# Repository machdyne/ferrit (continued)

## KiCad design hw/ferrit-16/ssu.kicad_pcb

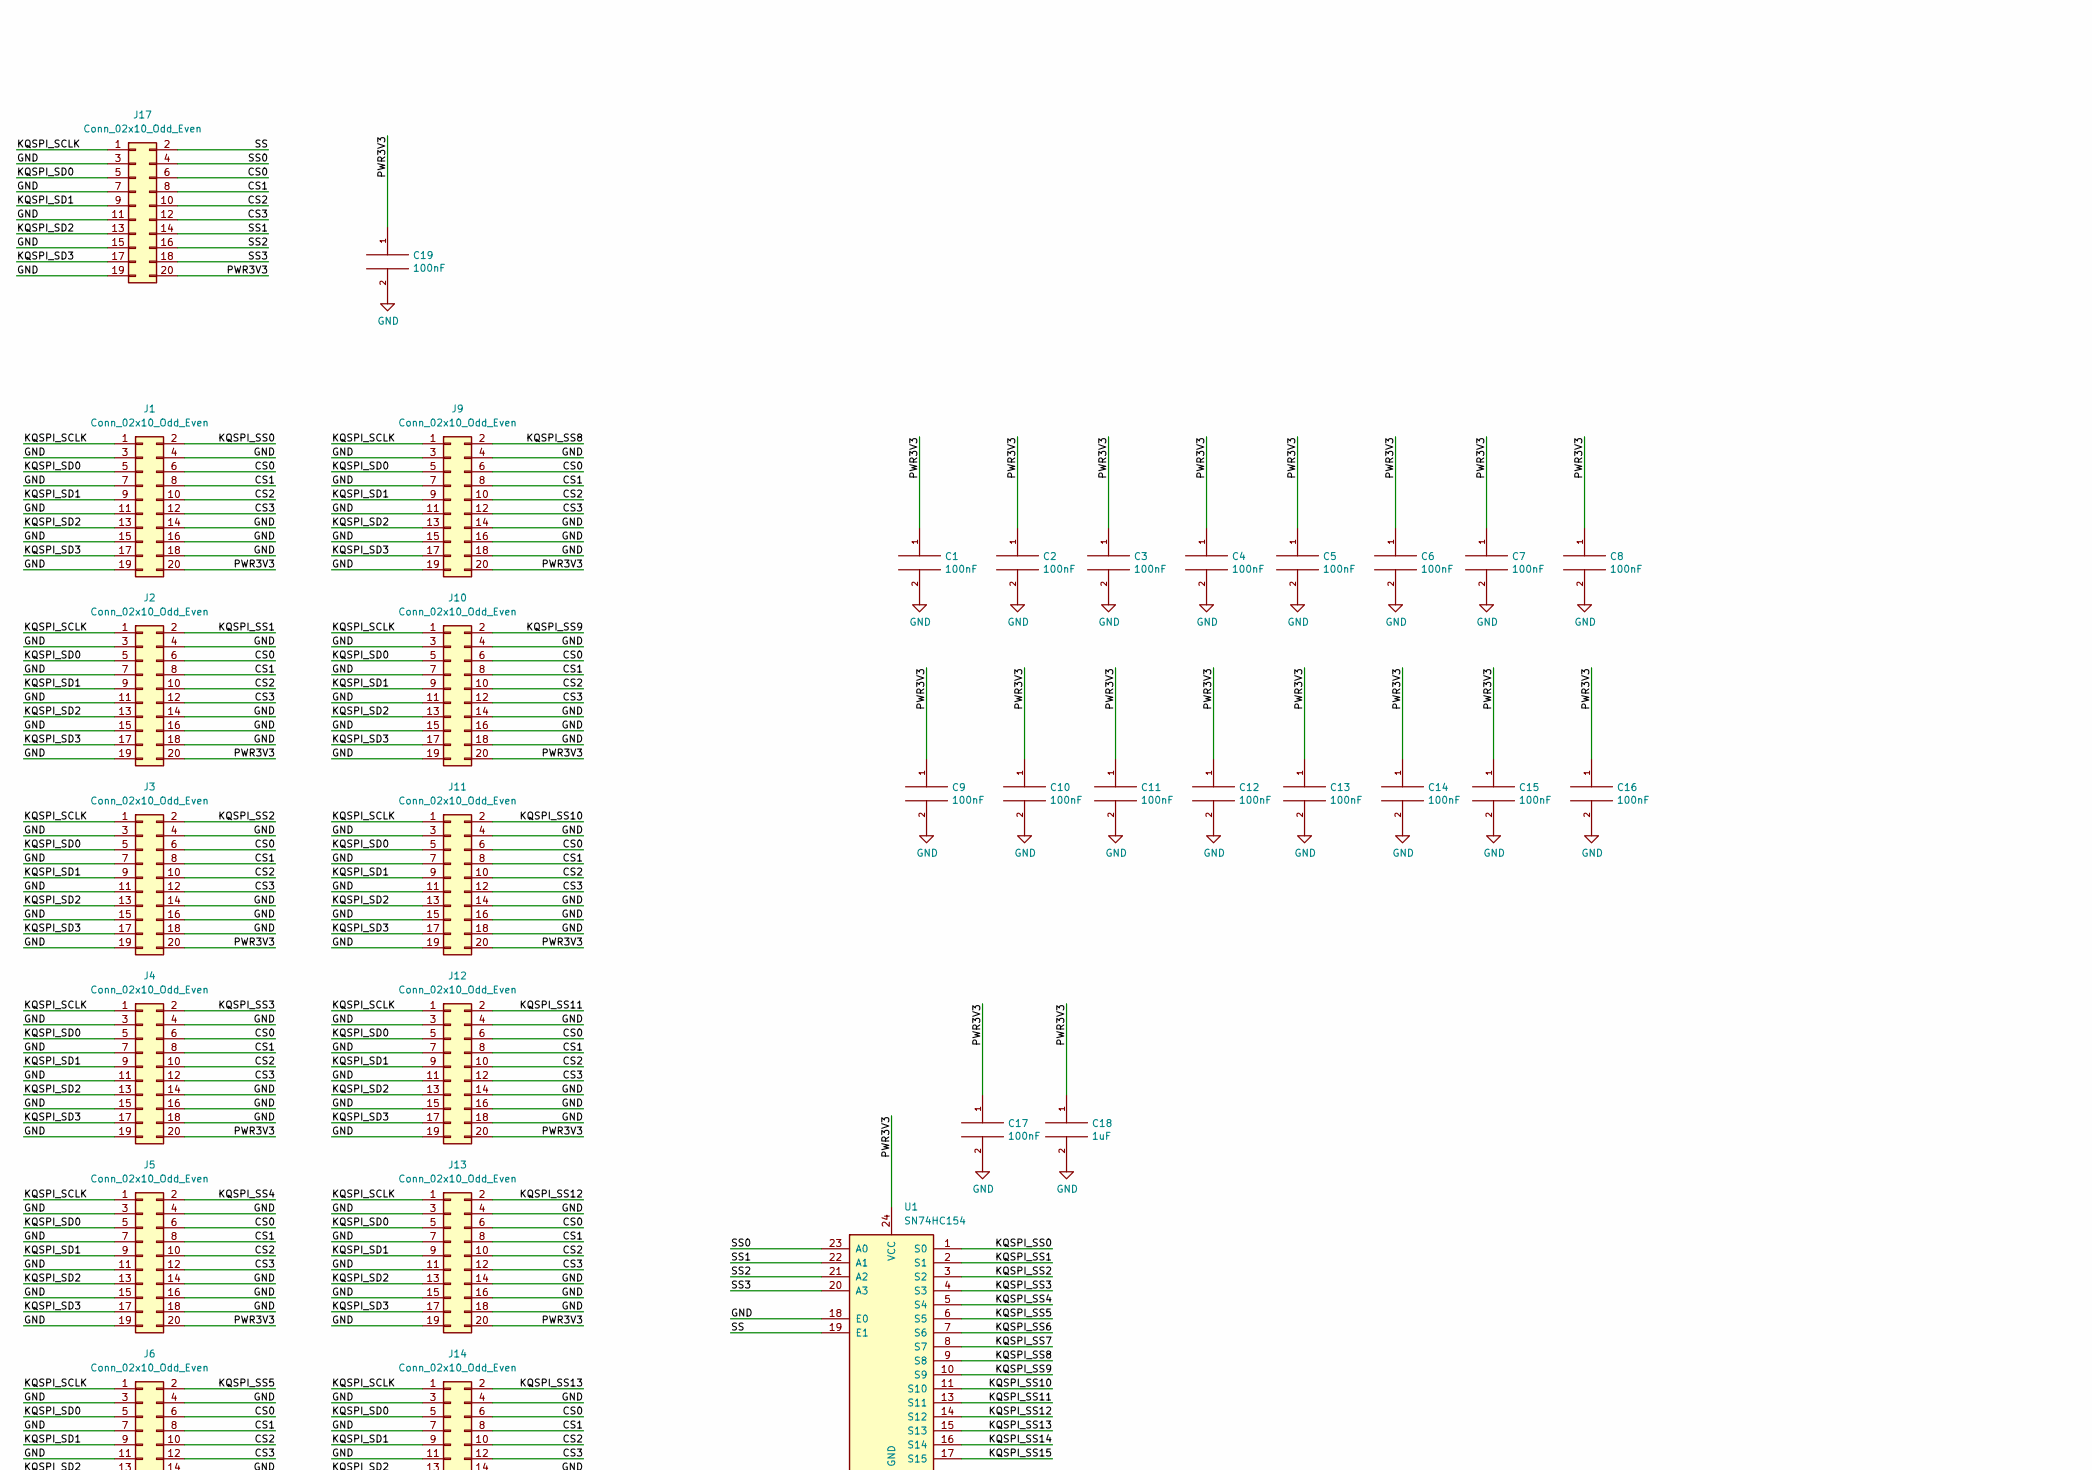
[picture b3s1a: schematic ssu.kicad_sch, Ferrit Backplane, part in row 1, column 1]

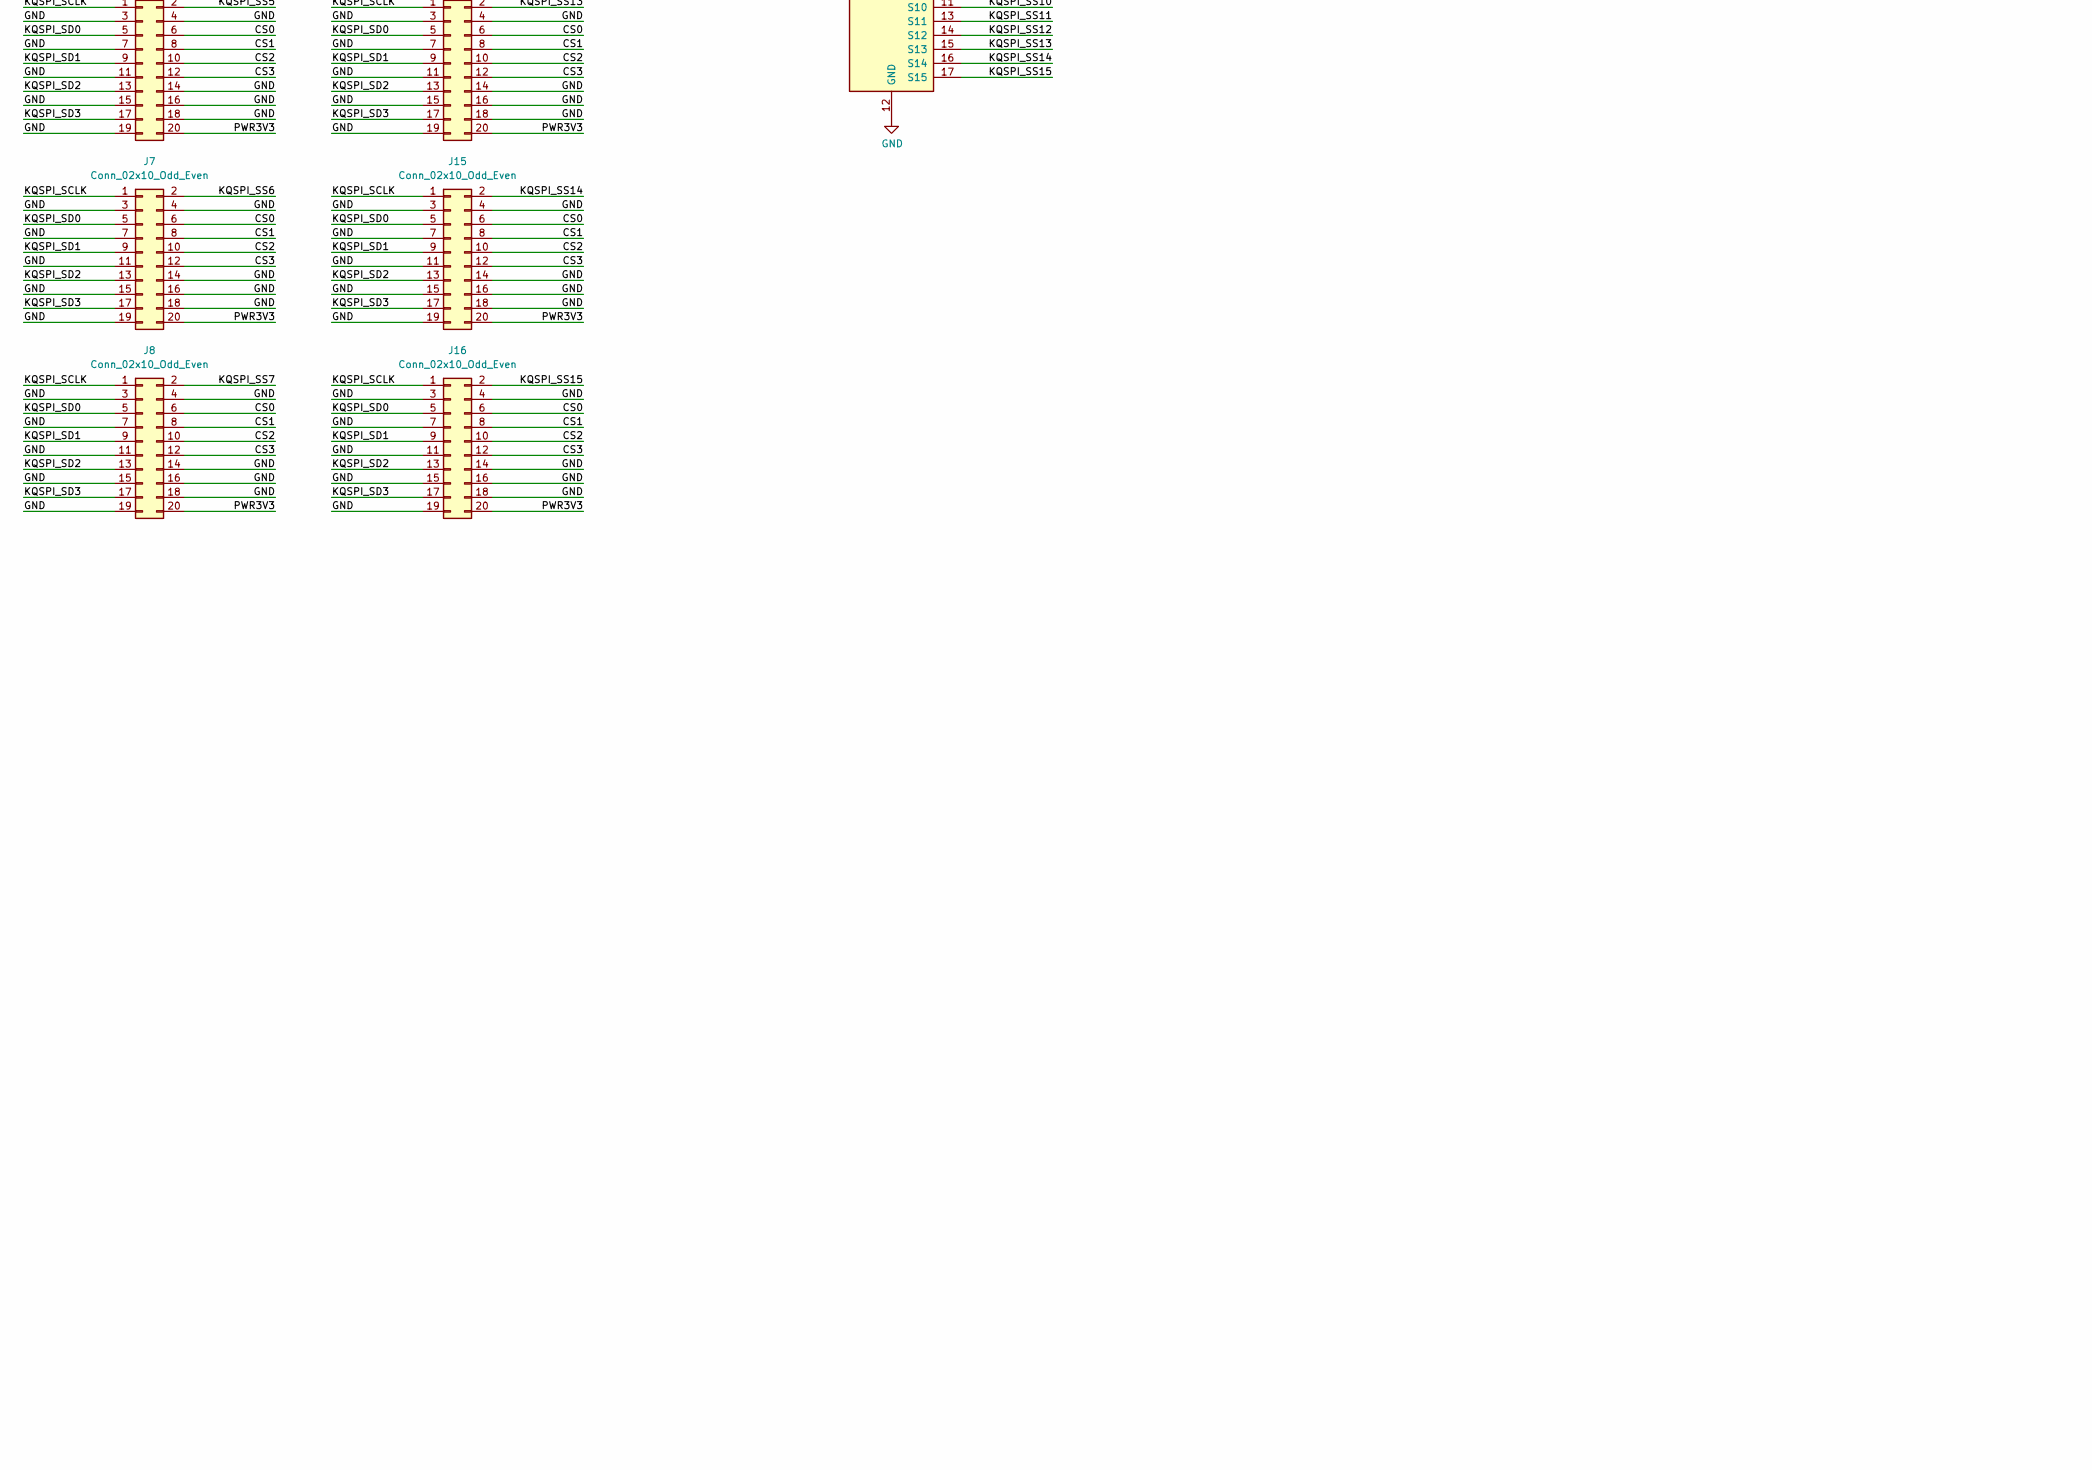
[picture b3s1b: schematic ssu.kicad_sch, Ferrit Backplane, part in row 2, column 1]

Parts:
C1, C2, C3, C4, C5, C6, C7, C8, C9, C10, C11, C12, C13, C14, C15, C16, C17, C19: 100nF; C_0603_1608Metric
C18: 1uF; C_0603_1608Metric
H1, H2: MountingHole; MountingHole_3.2mm_M3_DIN965_Pad
J1, J2, J3, J4, J5, J6, J7, J8, J9, J10, J11, J12, J13, J14, J15, J16, J17: Conn_02x10_Odd_Even; MACHDYNE_EDGE_SOCKET_20P
U1: SN74HC154; TSSOP-24_4.4x7.8mm_P0.65mm

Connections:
/CS0: J1.6, J2.6, J3.6, J4.6, J5.6, J6.6, J7.6, J8.6, J9.6, J10.6, J11.6, J12.6, J13.6, J14.6, J15.6, J16.6, J17.6
/CS1: J1.8, J2.8, J3.8, J4.8, J5.8, J6.8, J7.8, J8.8, J9.8, J10.8, J11.8, J12.8, J13.8, J14.8, J15.8, J16.8, J17.8
/CS2: J1.10, J2.10, J3.10, J4.10, J5.10, J6.10, J7.10, J8.10, J9.10, J10.10, J11.10, J12.10, J13.10, J14.10, J15.10, J16.10, J17.10
/CS3: J1.12, J2.12, J3.12, J4.12, J5.12, J6.12, J7.12, J8.12, J9.12, J10.12, J11.12, J12.12, J13.12, J14.12, J15.12, J16.12, J17.12
/KQSPI_SCLK: J1.1, J2.1, J3.1, J4.1, J5.1, J6.1, J7.1, J8.1, J9.1, J10.1, J11.1, J12.1, J13.1, J14.1, J15.1, J16.1, J17.1
/KQSPI_SD0: J1.5, J2.5, J3.5, J4.5, J5.5, J6.5, J7.5, J8.5, J9.5, J10.5, J11.5, J12.5, J13.5, J14.5, J15.5, J16.5, J17.5
/KQSPI_SD1: J1.9, J2.9, J3.9, J4.9, J5.9, J6.9, J7.9, J8.9, J9.9, J10.9, J11.9, J12.9, J13.9, J14.9, J15.9, J16.9, J17.9
/KQSPI_SD2: J1.13, J2.13, J3.13, J4.13, J5.13, J6.13, J7.13, J8.13, J9.13, J10.13, J11.13, J12.13, J13.13, J14.13, J15.13, J16.13, J17.13
/KQSPI_SD3: J1.17, J2.17, J3.17, J4.17, J5.17, J6.17, J7.17, J8.17, J9.17, J10.17, J11.17, J12.17, J13.17, J14.17, J15.17, J16.17, J17.17
/KQSPI_SS0: J1.2, U1.1 (S0)
/KQSPI_SS1: J2.2, U1.2 (S1)
/KQSPI_SS2: J3.2, U1.3 (S2)
/KQSPI_SS3: J4.2, U1.4 (S3)
/KQSPI_SS4: J5.2, U1.5 (S4)
/KQSPI_SS5: J6.2, U1.6 (S5)
/KQSPI_SS6: J7.2, U1.7 (S6)
/KQSPI_SS7: J8.2, U1.8 (S7)
/KQSPI_SS8: J9.2, U1.9 (S8)
/KQSPI_SS9: J10.2, U1.10 (S9)
/KQSPI_SS10: J11.2, U1.11 (S10)
/KQSPI_SS11: J12.2, U1.13 (S11)
/KQSPI_SS12: J13.2, U1.14 (S12)
/KQSPI_SS13: J14.2, U1.15 (S13)
/KQSPI_SS14: J15.2, U1.16 (S14)
/KQSPI_SS15: J16.2, U1.17 (S15)
/PWR3V3: C1.1, C2.1, C3.1, C4.1, C5.1, C6.1, C7.1, C8.1, C9.1, C10.1, C11.1, C12.1, C13.1, C14.1, C15.1, C16.1, C17.1, C18.1, C19.1, J1.20, J2.20, J3.20, J4.20, J5.20, J6.20, J7.20, J8.20, J9.20, J10.20, J11.20, J12.20, J13.20, J14.20, J15.20, J16.20, J17.20, U1.24 (VCC)
/SS: J17.2, U1.19 (E1)
/SS0: J17.4, U1.23 (A0)
/SS1: J17.14, U1.22 (A1)
/SS2: J17.16, U1.21 (A2)
/SS3: J17.18, U1.20 (A3)
GND: C1.2, C2.2, C3.2, C4.2, C5.2, C6.2, C7.2, C8.2, C9.2, C10.2, C11.2, C12.2, C13.2, C14.2, C15.2, C16.2, C17.2, C18.2, C19.2, J1.3, J1.4, J1.7, J1.11, J1.14, J1.15, J1.16, J1.18, J1.19, J2.3, J2.4, J2.7, J2.11, J2.14, J2.15, J2.16, J2.18, J2.19, J3.3, J3.4, J3.7, J3.11, J3.14, J3.15, J3.16, J3.18, J3.19, J4.3, J4.4, J4.7, J4.11, J4.14, J4.15, J4.16, J4.18, J4.19, J5.3, J5.4, J5.7, J5.11, J5.14, J5.15, J5.16, J5.18, J5.19, J6.3, J6.4, J6.7, J6.11, J6.14, J6.15, J6.16, J6.18, J6.19, J7.3, J7.4, J7.7, J7.11, J7.14, J7.15, J7.16, J7.18, J7.19, J8.3, J8.4, J8.7, J8.11, J8.14, J8.15, J8.16, J8.18, J8.19, J9.3, J9.4, J9.7, J9.11, J9.14, J9.15, J9.16, J9.18, J9.19, J10.3, J10.4, J10.7, J10.11, J10.14, J10.15, J10.16, J10.18, J10.19, J11.3, J11.4, J11.7, J11.11, J11.14, J11.15, J11.16, J11.18, J11.19, J12.3, J12.4, J12.7, J12.11, J12.14, J12.15, J12.16, J12.18, J12.19, J13.3, J13.4, J13.7, J13.11, J13.14, J13.15, J13.16, J13.18, J13.19, J14.3, J14.4, J14.7, J14.11, J14.14, J14.15, J14.16, J14.18, J14.19, J15.3, J15.4, J15.7, J15.11, J15.14, J15.15, J15.16, J15.18, J15.19, J16.3, J16.4, J16.7, J16.11, J16.14, J16.15, J16.16, J16.18, J16.19, J17.3, J17.7, J17.11, J17.15, J17.19, U1.12 (GND), U1.18 (E0)

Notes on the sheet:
U B E R S T A H L
FERRIT-16

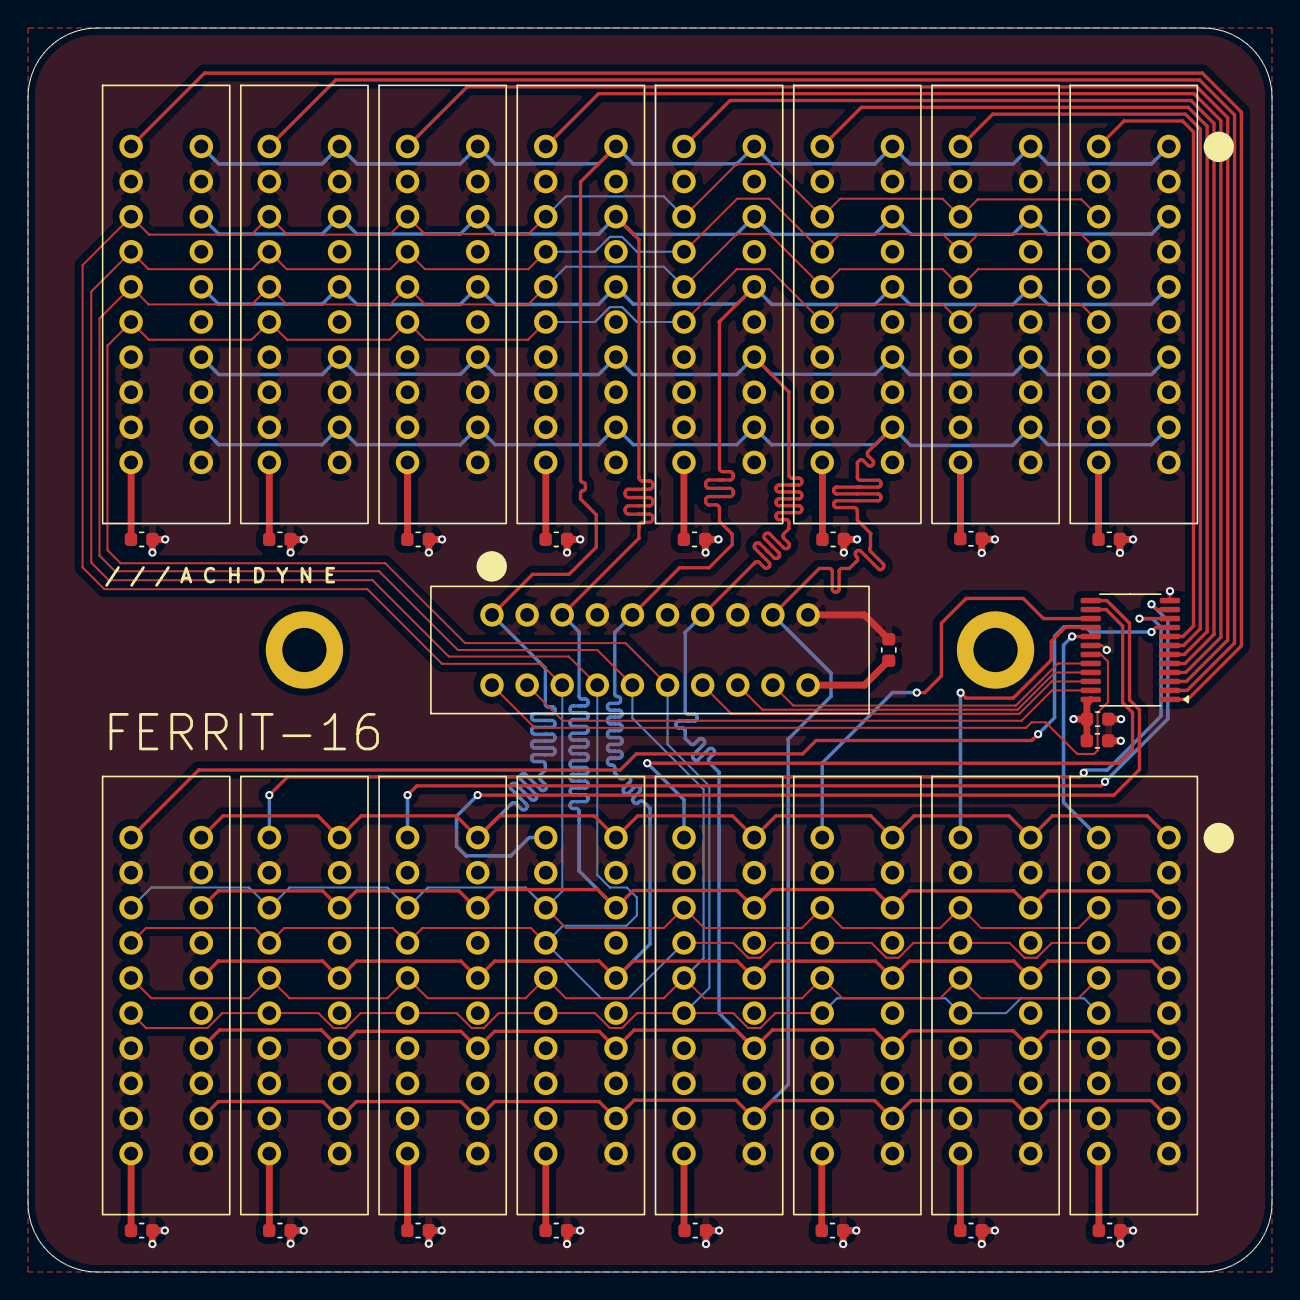
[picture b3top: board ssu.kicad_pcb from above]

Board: 4 copper layers, 90.0 x 90.0 mm, 39 parts (0 on the bottom side), 32 nets.

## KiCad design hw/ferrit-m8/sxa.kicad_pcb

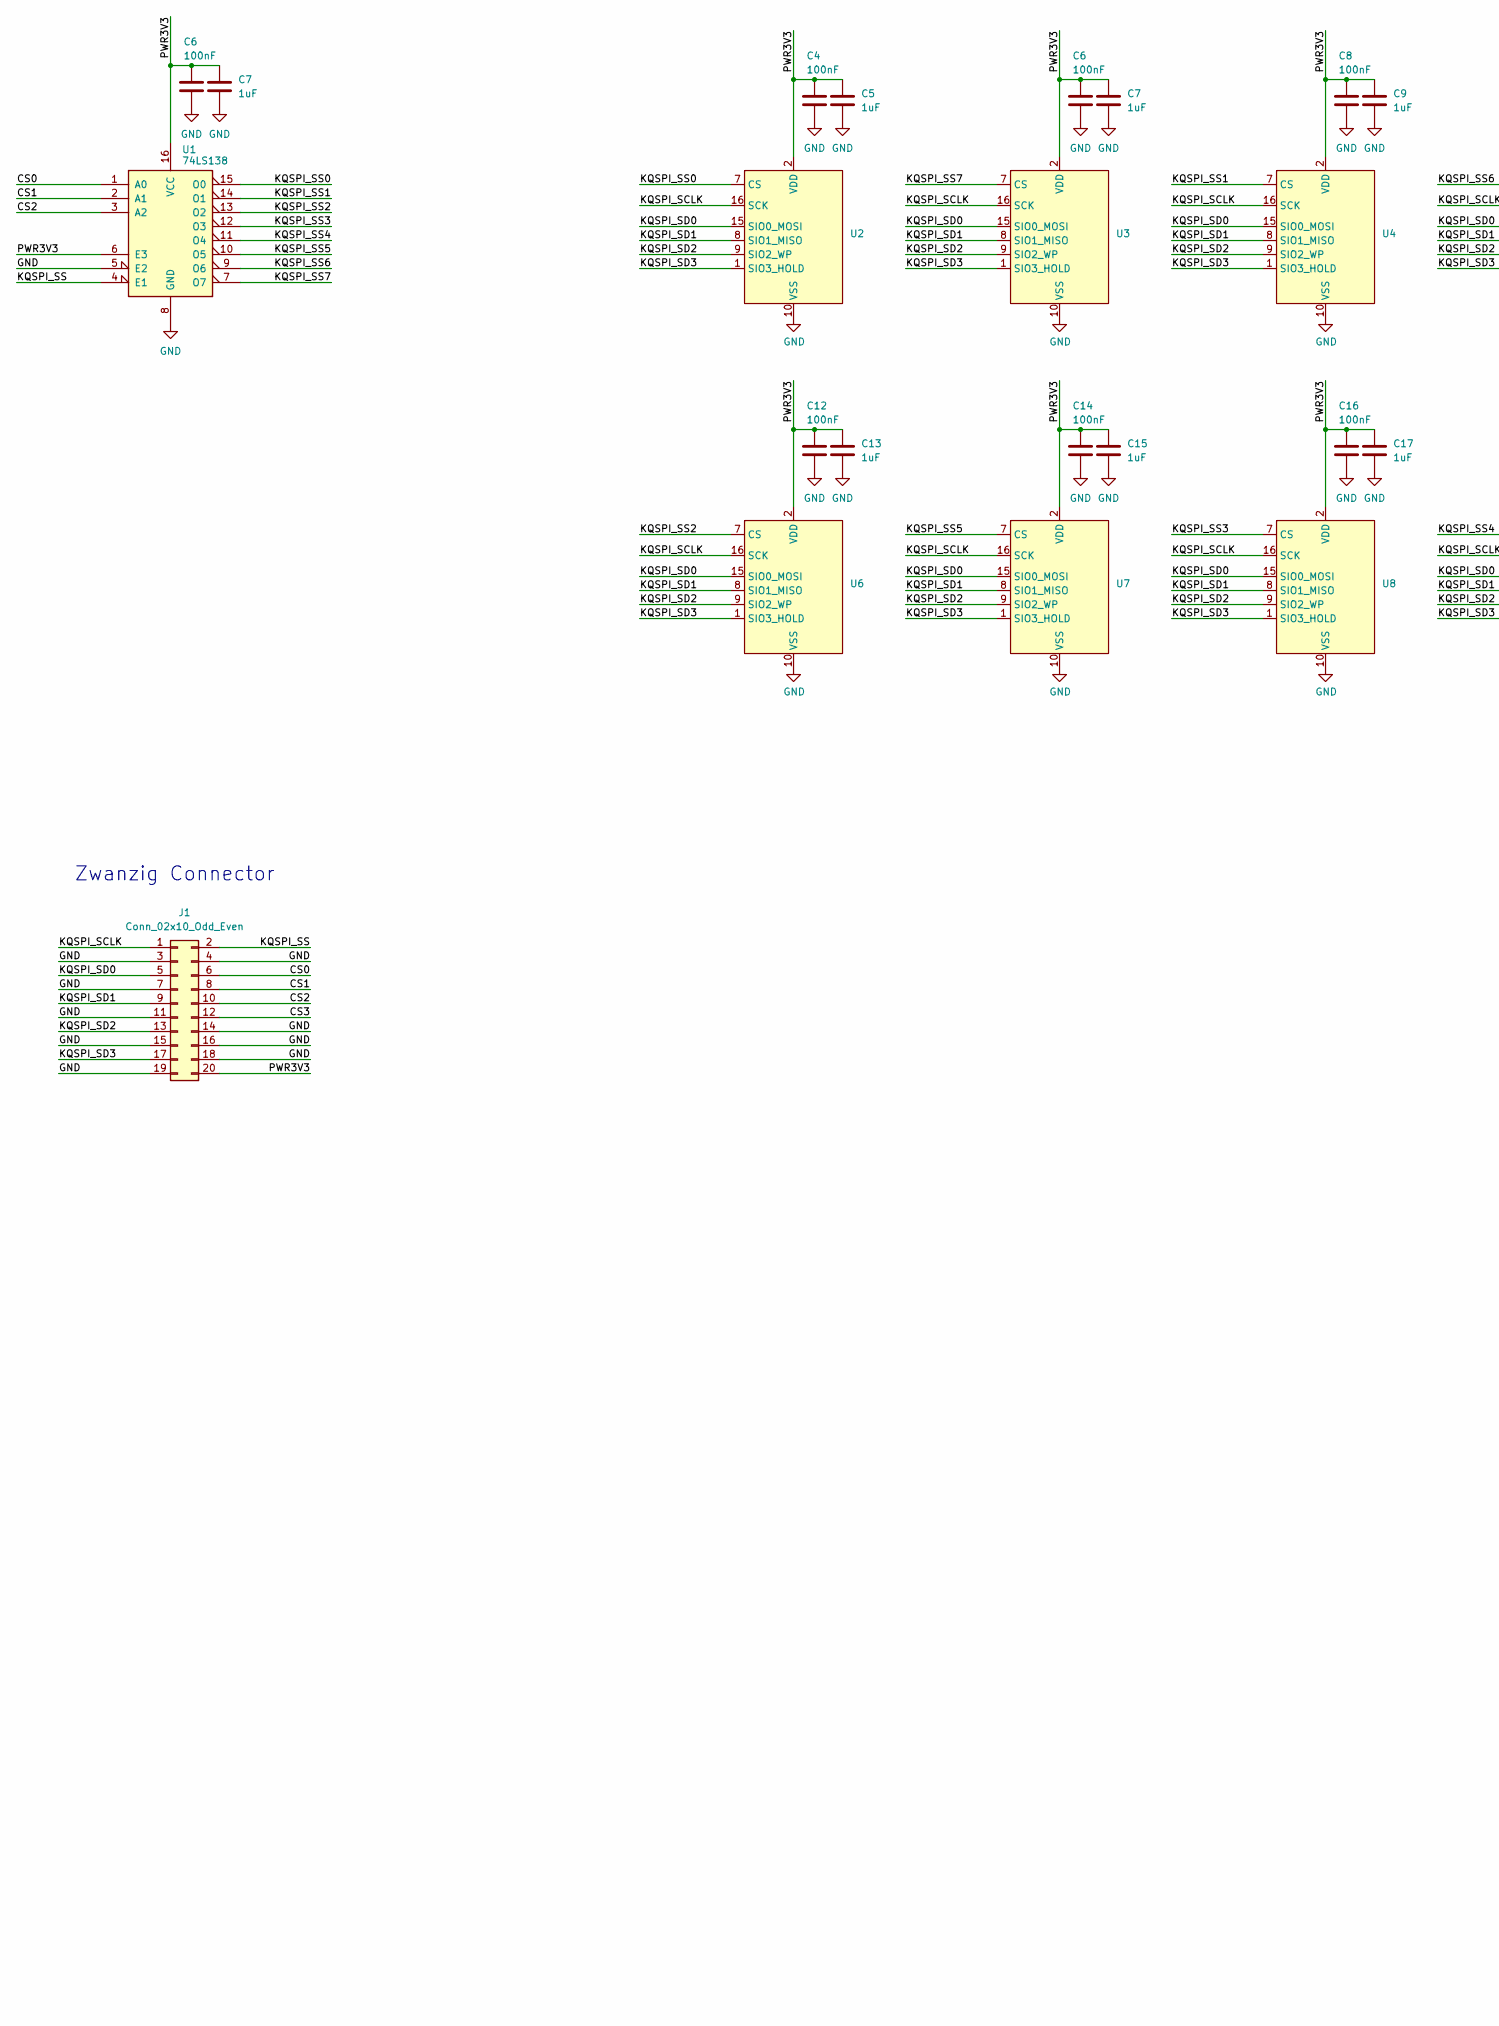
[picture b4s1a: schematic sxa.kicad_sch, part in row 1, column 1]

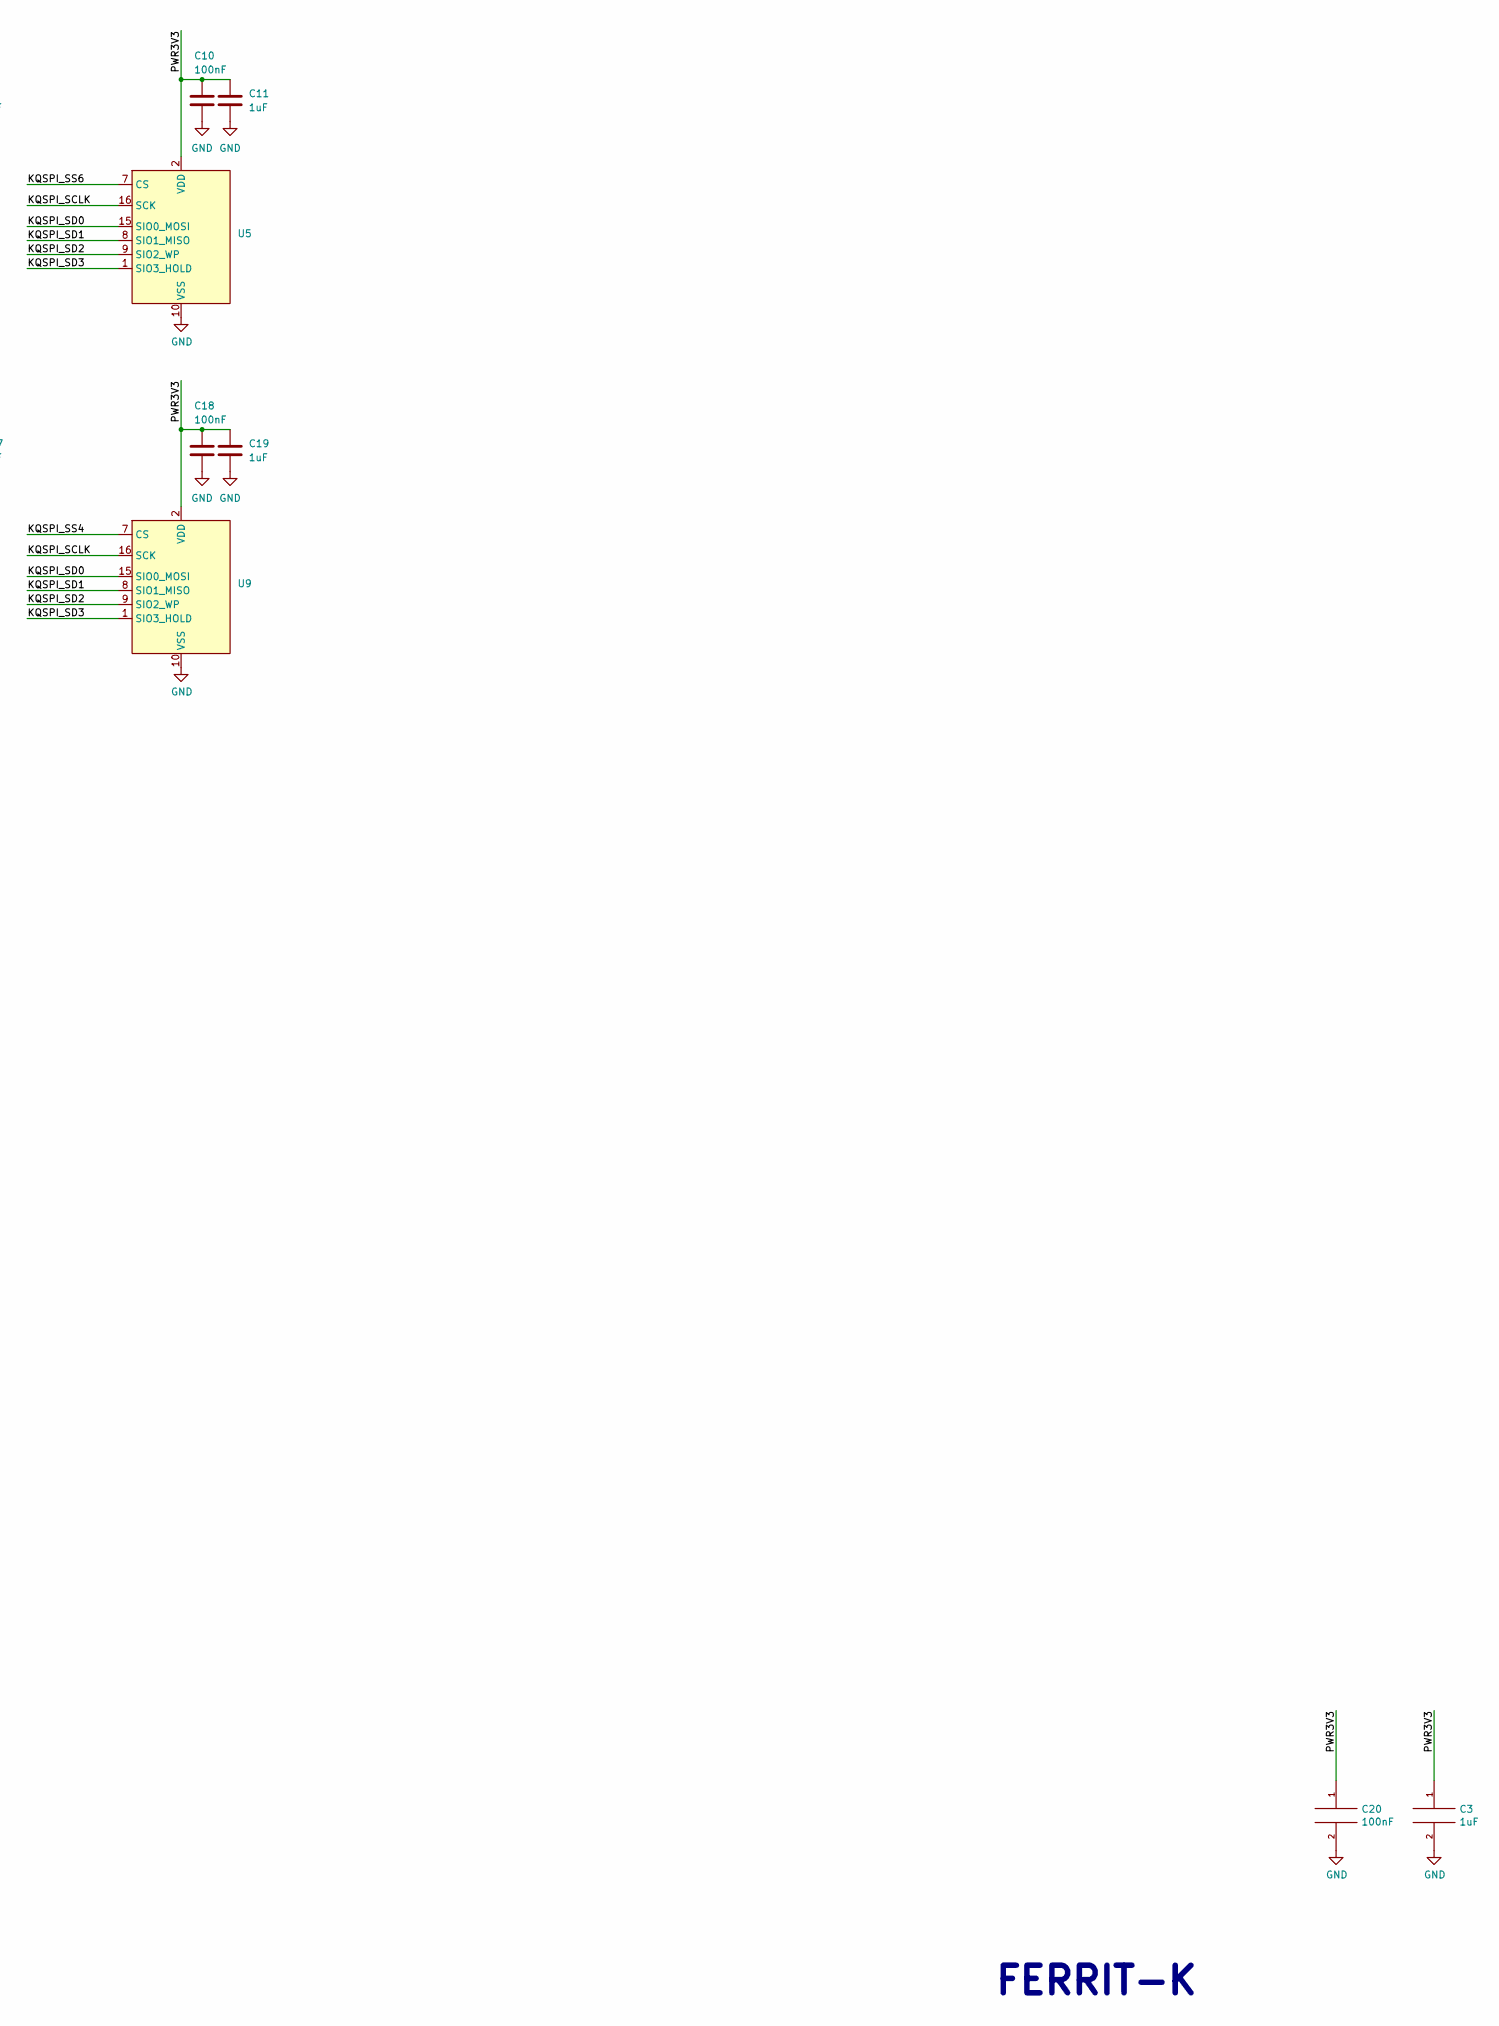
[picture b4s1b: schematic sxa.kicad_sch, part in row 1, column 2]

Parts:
C3, C5, C7, C9, C11, C13, C15, C17, C19: 1uF; C_0603_1608Metric
C4, C6, C8, C10, C12, C14, C16, C18, C20: 100nF; C_0603_1608Metric
J1: Conn_02x10_Odd_Even; MACHDYNE_EDGE_20P
U1: 74LS138; TSSOP-16_4.4x5mm_P0.65mm
U2, U3, U4, U5, U6, U7, U8, U9: SOIC-16W_7.5x10.3mm_P1.27mm

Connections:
/CS0: J1.6, U1.1 (A0)
/CS1: J1.8, U1.2 (A1)
/CS2: J1.10, U1.3 (A2)
/CS3: J1.12
/KQSPI_SCLK: J1.1, U2.16 (SCK), U3.16 (SCK), U4.16 (SCK), U5.16 (SCK), U6.16 (SCK), U7.16 (SCK), U8.16 (SCK), U9.16 (SCK)
/KQSPI_SD0: J1.5, U2.15 (SIO0_MOSI), U3.15 (SIO0_MOSI), U4.15 (SIO0_MOSI), U5.15 (SIO0_MOSI), U6.15 (SIO0_MOSI), U7.15 (SIO0_MOSI), U8.15 (SIO0_MOSI), U9.15 (SIO0_MOSI)
/KQSPI_SD1: J1.9, U2.8 (SIO1_MISO), U3.8 (SIO1_MISO), U4.8 (SIO1_MISO), U5.8 (SIO1_MISO), U6.8 (SIO1_MISO), U7.8 (SIO1_MISO), U8.8 (SIO1_MISO), U9.8 (SIO1_MISO)
/KQSPI_SD2: J1.13, U2.9 (SIO2_WP), U3.9 (SIO2_WP), U4.9 (SIO2_WP), U5.9 (SIO2_WP), U6.9 (SIO2_WP), U7.9 (SIO2_WP), U8.9 (SIO2_WP), U9.9 (SIO2_WP)
/KQSPI_SD3: J1.17, U2.1 (SIO3_HOLD), U3.1 (SIO3_HOLD), U4.1 (SIO3_HOLD), U5.1 (SIO3_HOLD), U6.1 (SIO3_HOLD), U7.1 (SIO3_HOLD), U8.1 (SIO3_HOLD), U9.1 (SIO3_HOLD)
/KQSPI_SS: J1.2, U1.4 (E1)
/KQSPI_SS0: U1.15 (O0), U2.7 (CS)
/KQSPI_SS1: U1.14 (O1), U4.7 (CS)
/KQSPI_SS2: U1.13 (O2), U6.7 (CS)
/KQSPI_SS3: U1.12 (O3), U8.7 (CS)
/KQSPI_SS4: U1.11 (O4), U9.7 (CS)
/KQSPI_SS5: U1.10 (O5), U7.7 (CS)
/KQSPI_SS6: U1.9 (O6), U5.7 (CS)
/KQSPI_SS7: U1.7 (O7), U3.7 (CS)
/PWR3V3: C3.1, C4.1, C5.1, C6.1, C7.1, C8.1, C9.1, C10.1, C11.1, C12.1, C13.1, C14.1, C15.1, C16.1, C17.1, C18.1, C19.1, C20.1, J1.20, U1.6 (E3), U1.16 (VCC), U2.2 (VDD), U3.2 (VDD), U4.2 (VDD), U5.2 (VDD), U6.2 (VDD), U7.2 (VDD), U8.2 (VDD), U9.2 (VDD); also elsewhere on the board
GND: C3.2, C4.2, C5.2, C6.2, C7.2, C8.2, C9.2, C10.2, C11.2, C12.2, C13.2, C14.2, C15.2, C16.2, C17.2, C18.2, C19.2, C20.2, J1.3, J1.4, J1.7, J1.11, J1.14, J1.15, J1.16, J1.18, J1.19, U1.5 (E2), U1.8 (GND), U2.10 (VSS), U3.10 (VSS), U4.10 (VSS), U5.10 (VSS), U6.10 (VSS), U7.10 (VSS), U8.10 (VSS), U9.10 (VSS); also elsewhere on the board

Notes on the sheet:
FERRIT-K
Zwanzig Connector

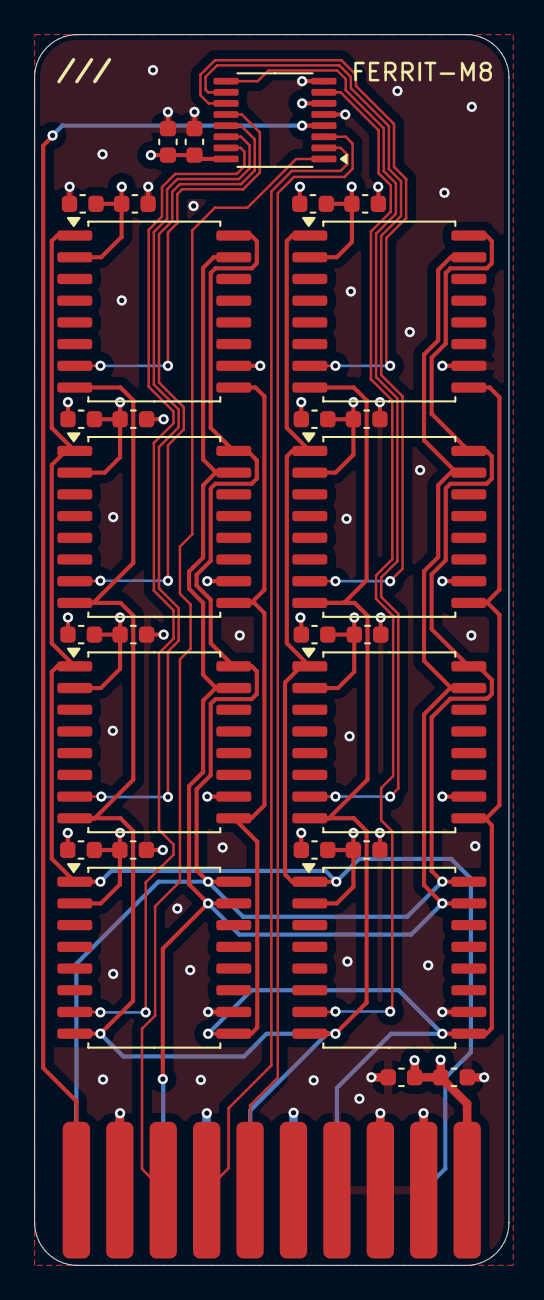
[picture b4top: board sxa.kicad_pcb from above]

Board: 4 copper layers, 27.8 x 72.0 mm, 30 parts (0 on the bottom side), 19 nets.

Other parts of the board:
C1: 100nF; C_0603_1608Metric
C2: 1uF; C_0603_1608Metric

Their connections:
/PWR3V3: C1.1, C2.1; also elsewhere on the board
GND: C1.2, C2.2; also elsewhere on the board

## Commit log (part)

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2026-03-31 add prototype hardware designs
2026-03-31 add renders
2026-03-31 resize renders
2026-04-04 cleanup schematics
2026-04-05 add pinouts
2026-04-06 update designs
2026-04-06 update render
2026-04-30 add firmware
2026-06-12 add ferrit-1 (edelstahl)
2026-06-28 add edelstahl case
